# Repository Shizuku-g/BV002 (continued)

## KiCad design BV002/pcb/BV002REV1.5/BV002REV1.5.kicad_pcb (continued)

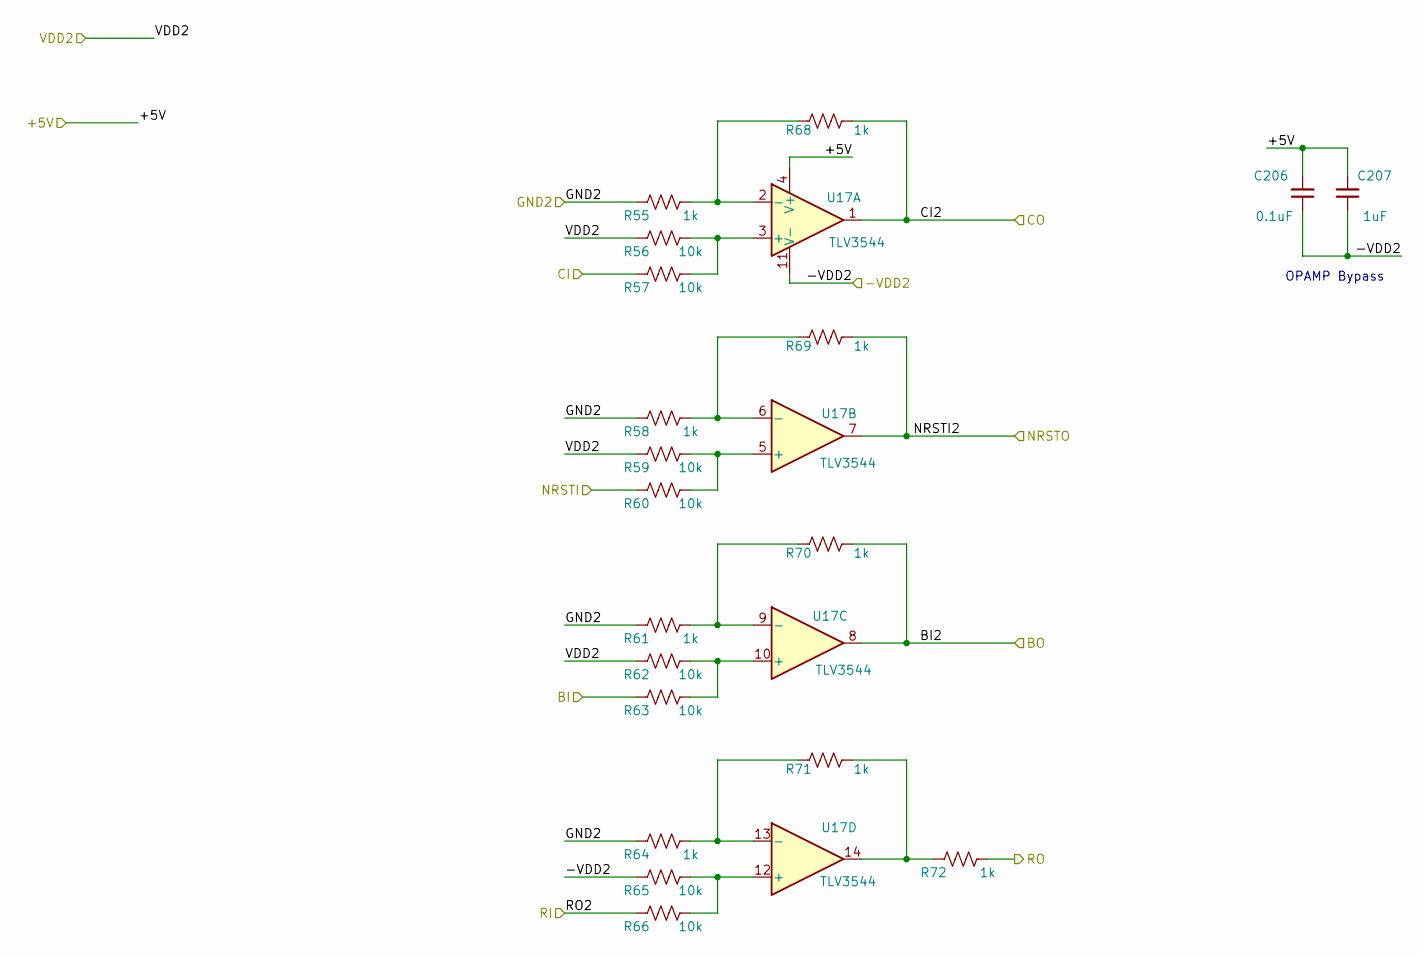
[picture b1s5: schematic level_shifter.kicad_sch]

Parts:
C206: 0.1uF; C_0402_1005Metric; PARTNO KGM05AR71C104KH
C207: 1uF; C_0402_1005Metric; PARTNO EMK105BJ105MV-F
R55, R58, R61, R64, R68, R69, R70, R71, R72: 1k; R_0402_1005Metric; PARTNO RC0402FR-071KL
R56, R57, R59, R60, R62, R63, R65, R66: 10k; R_0402_1005Metric; PARTNO RC0402JR-0710KL
U17: TLV3544; TSSOP-14_4.4x5mm_P0.65mm; PARTNO TLV3544IPWR

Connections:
+5V: C206.2, C207.2, U17.4 (V+); also elsewhere on the board
/BM1373/Level Shifter/BI: R63.1; also elsewhere on the board
/BM1373/Level Shifter/BI2: R70.1, U17.8; also elsewhere on the board
/BM1373/Level Shifter/CI: R57.1; also elsewhere on the board
/BM1373/Level Shifter/CI2: R68.1, U17.1; also elsewhere on the board
/BM1373/Level Shifter/NRSTI: R60.1; also elsewhere on the board
/BM1373/Level Shifter/NRSTI2: R69.1, U17.7; also elsewhere on the board
/BM1373/Level Shifter/RO: R72.1; also elsewhere on the board
/BM1373/Level Shifter/RO2: R66.1; also elsewhere on the board
unnamed: R71.1, R72.2, U17.14
unnamed: R56.1, R57.2, U17.3 (+)
unnamed: R55.1, R68.2, U17.2 (-)
unnamed: R59.2, R60.2, U17.5 (+)
unnamed: R58.1, R69.2, U17.6 (-)
unnamed: R62.2, R63.2, U17.10 (+)
unnamed: R61.1, R70.2, U17.9 (-)
unnamed: R65.2, R66.2, U17.12 (+)
unnamed: R64.1, R71.2, U17.13 (-)
VDD: R56.2, R59.1, R62.1; also elsewhere on the board
VDD1: R55.2, R58.2, R61.2, R64.2; also elsewhere on the board

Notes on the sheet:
OPAMP Bypass

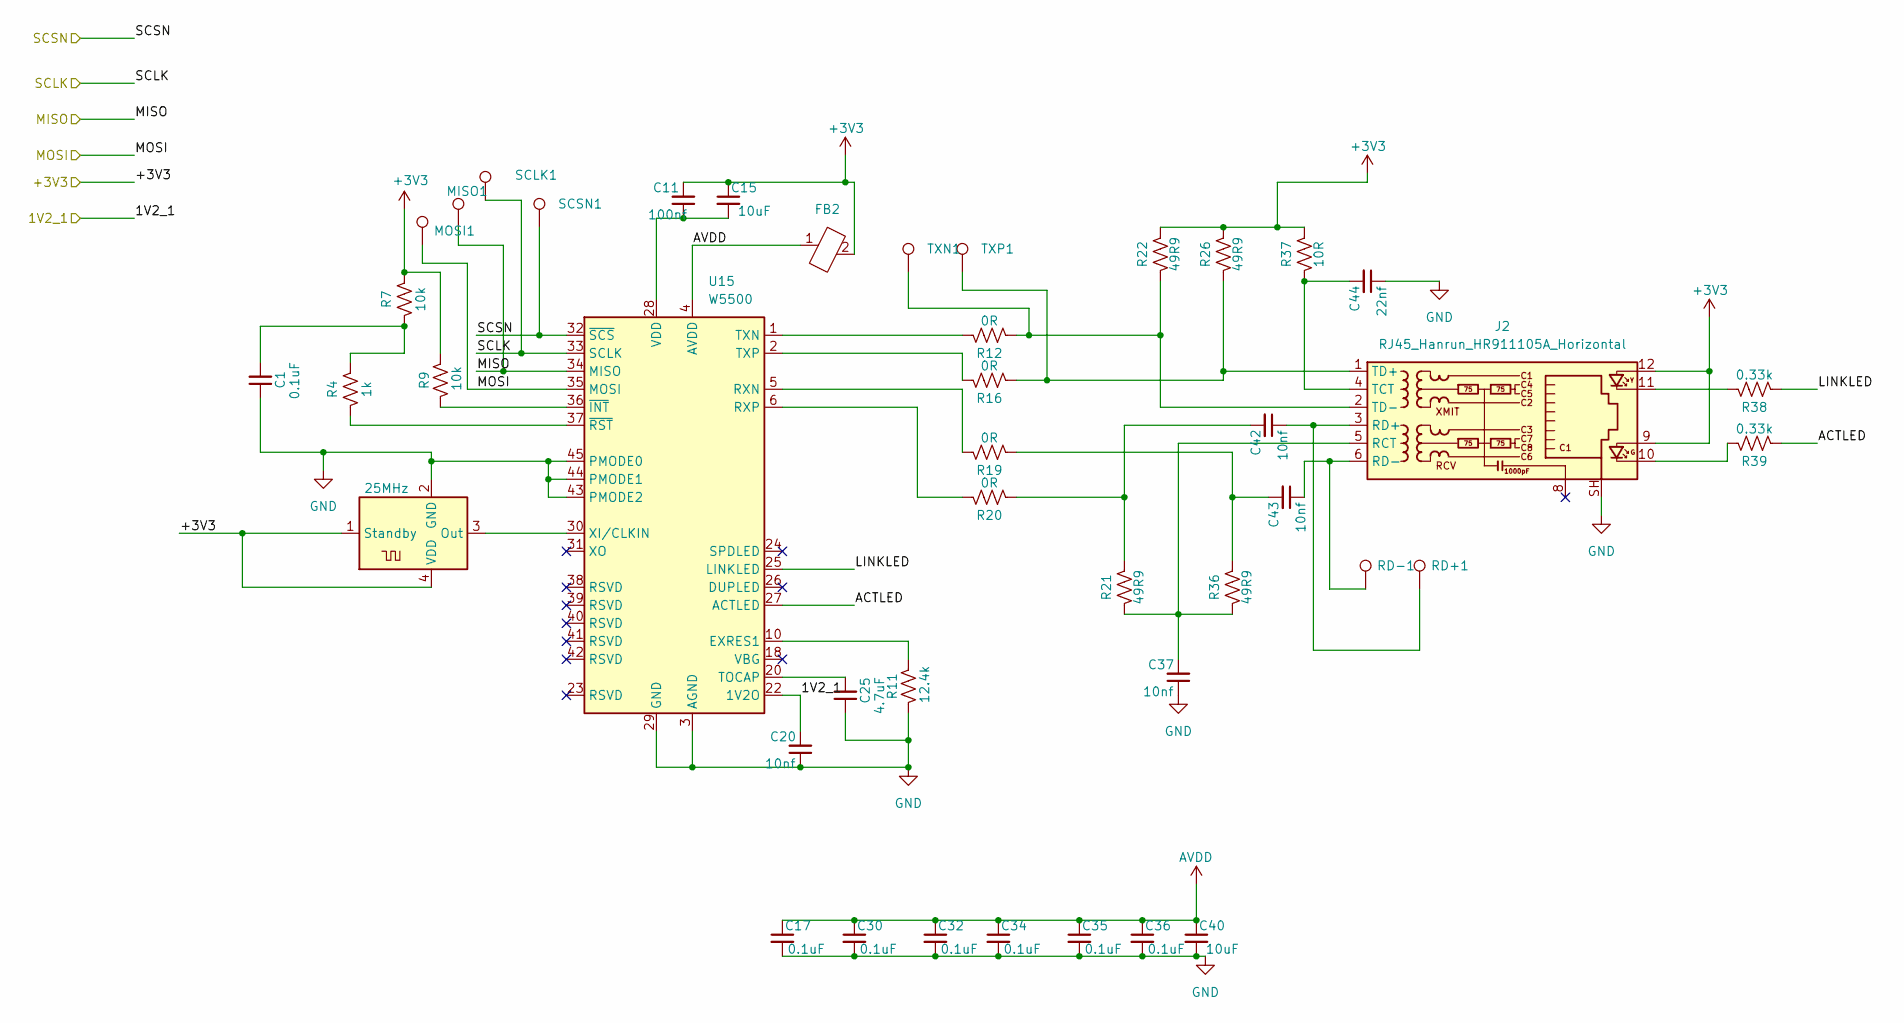
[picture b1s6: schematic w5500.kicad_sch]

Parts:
C1: 0.1uF; C_0402_1005Metric; PARTNO GRM155R61A475MEAAD
C11: 100nf; C_0402_1005Metric; PARTNO GRM188R61E106KA73D
C15, C40: 10uF; C_0603_1608Metric; PARTNO CL10A106MO8NQNC; LCSC C92487 Hot
C17, C30, C32, C34, C35, C36: 0.1uF; C_0603_1608Metric; PARTNO CL10A106MO8NQNC; LCSC C92487 Hot
C20, C37, C42, C43: 10nf; C_0402_1005Metric; PARTNO GRM188R61E106KA73D
C25: 4.7uF; C_0402_1005Metric; PARTNO GRM155R61A475MEAAD
C44: 22nf; C_0402_1005Metric; PARTNO GRM188R61E106KA73D
FB2: D_0201_0603Metric
J2: RJ45_Hanrun_HR911105A_Horizontal
MISO1: TestPoint_Pad_D1.5mm
MOSI1: TestPoint_Pad_D1.5mm
R4: 1k; R_0402_1005Metric; PARTNO RC0402FR-071KL; LCSC C106235
R7: 10k; R_0402_1005Metric; PARTNO RC0402FR-071KL; LCSC C106235
R9: 10k; R_0402_1005Metric; PARTNO RC0402FR-072KL; LCSC C60488
R11: 12.4k; R_0402_1005Metric; PARTNO RC0402FR-072KL; LCSC C60488
R12, R16, R19, R20: 0R; R_0402_1005Metric; PARTNO RC0402FR-071KL; LCSC C106235
R21, R22, R26, R36: 49R9; R_0402_1005Metric; PARTNO RC0402FR-071KL; LCSC C106235
R37: 10R; R_0402_1005Metric; PARTNO RC0402FR-071KL; LCSC C106235
R38, R39: 0.33k; R_0402_1005Metric; PARTNO RC0402FR-071KL; LCSC C106235
RD+1: TestPoint_Pad_D1.5mm
RD-1: TestPoint_Pad_D1.5mm
SCLK1: TestPoint_Pad_D1.5mm
SCSN1: TestPoint_Pad_D1.5mm
TXN1: TestPoint_Pad_D1.5mm
TXP1: TestPoint_Pad_D1.5mm
U2: 25MHz; Oscillator_SMD_EuroQuartz_XO32-4Pin_3.2x2.5mm; PARTNO SX3M25.000E20F30THN
U15: W5500; LQFP-48_7x7mm_P0.5mm

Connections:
1V2_1: C20.2, U15.22 (1V2O); also elsewhere on the board
/T-Display-S3/MISO: MISO1.1 (1_1), U15.34 (MISO); also elsewhere on the board
/T-Display-S3/MOSI: MOSI1.1 (1_1), U15.35 (MOSI); also elsewhere on the board
/T-Display-S3/SCLK: SCLK1.1 (1_1), U15.33 (SCLK); also elsewhere on the board
/T-Display-S3/SCSN: SCSN1.1 (1_1), U15.32 (~SCS); also elsewhere on the board
/T-Display-S3/W5500/ACTLED: R39.2, U15.27 (ACTLED)
/T-Display-S3/W5500/LINKLED: R38.2, U15.25 (LINKLED)
unnamed: C1.2, R4.1, R7.2
unnamed: C42.2, R20.2, R21.1
unnamed: C43.2, R19.2, R36.1
unnamed: J2.10, R39.1
unnamed: J2.11, R38.1
unnamed: C37.2, J2.5 (RCT), R21.2, R36.2
unnamed: C42.1, J2.3 (RD+), RD+1.1 (1_1)
unnamed: C43.1, J2.6 (RD-), RD-1.1 (1_1)
unnamed: C44.2, J2.4 (TCT), R37.2
unnamed: J2.1 (TD+), R16.2, R26.2, TXP1.1 (1_1)
unnamed: J2.2 (TD-), R12.2, R22.2, TXN1.1 (1_1)
unnamed: R11.2, U15.10 (EXRES1)
unnamed: R19.1, U15.5 (RXN)
unnamed: R20.1, U15.6 (RXP)
unnamed: C25.2, U15.20 (TOCAP)
unnamed: R12.1, U15.1 (TXN)
unnamed: R16.1, U15.2 (TXP)
unnamed: C11.1, C15.2, U15.28 (VDD)
unnamed: U2.3 (Out), U15.30 (XI/CLKIN)
unnamed: R9.1, U15.36 (~INT)
unnamed: R4.2, U15.37 (~RST)

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
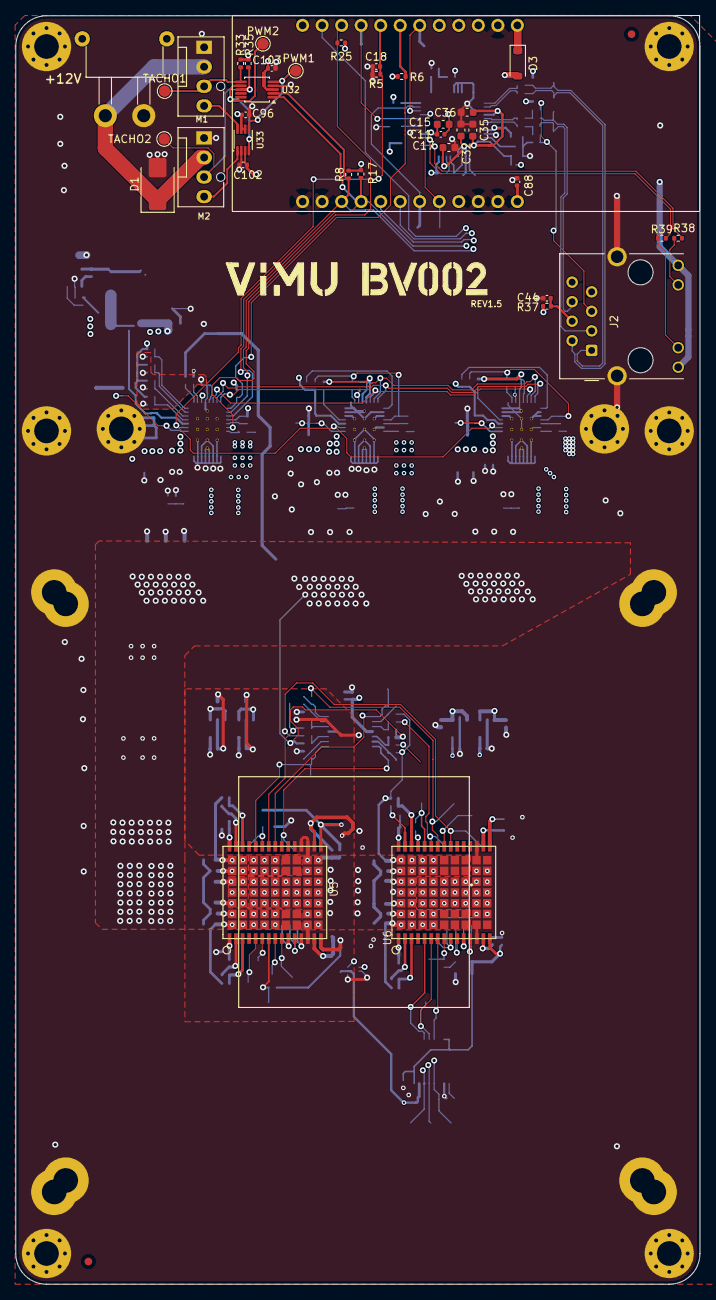
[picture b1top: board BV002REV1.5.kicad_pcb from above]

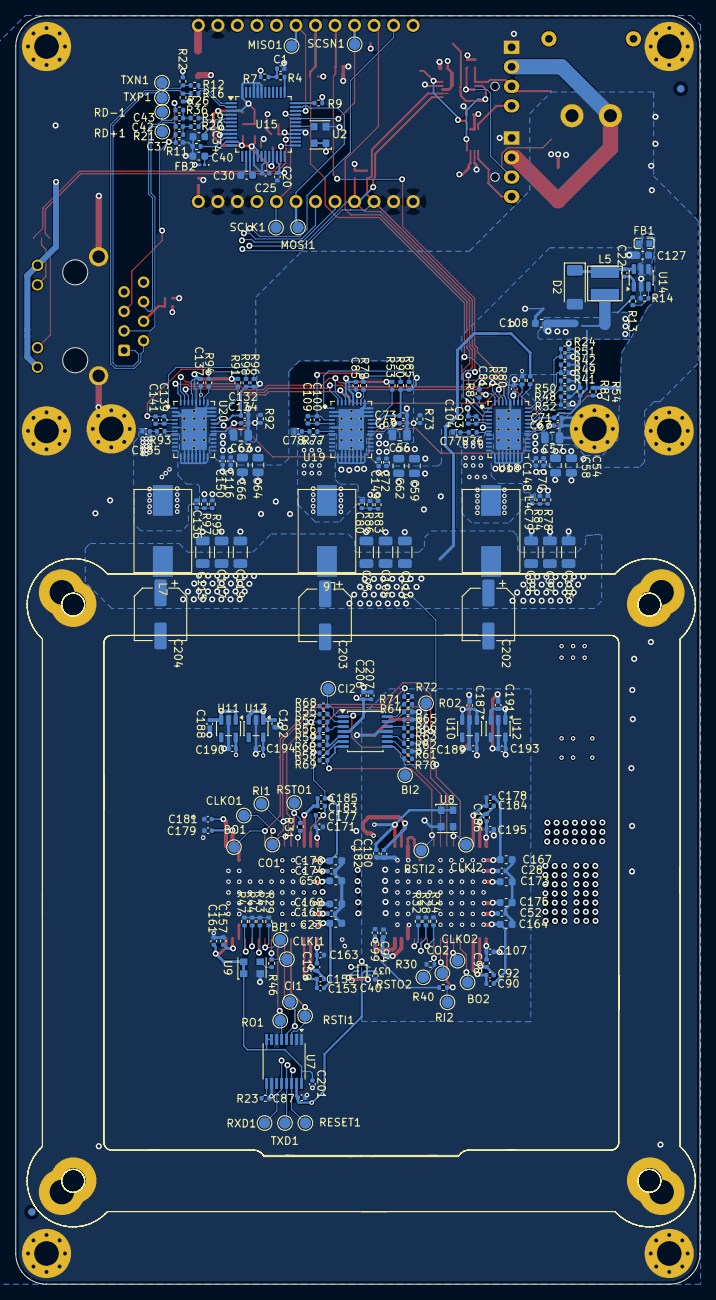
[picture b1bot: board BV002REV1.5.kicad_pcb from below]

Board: 4 copper layers, 89.0 x 165.0 mm, 289 parts (242 on the bottom side), 147 nets.

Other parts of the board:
C40#2: 10uF; C_0603_1608Metric
C201: 0.1uF; C_0402_1005Metric
C202, C203, C204: 270uF; CP_Elec_6.3x5.9
FID1, FID2, FID3, FID4: Fiducial_1mm_Mask2mm
H7, H8: MountingHole_Pad; MountingHole_3.2mm_M3_Pad_Via
R6: 10k; R_0402_1005Metric

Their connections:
1V2_1: C201.1; also elsewhere on the board
PGOOD: R6.1; also elsewhere on the board
VDD: C202.1, C203.1, C204.1; also elsewhere on the board

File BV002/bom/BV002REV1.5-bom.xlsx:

编号 | 位号 | 封装 | 数量 | 名称 | 供应商
1 | R46,R12,R16,R19,R20,R76,R77,R93 | R_0402_1005Metric 0R | 8
2 | R37,R54,R73,R78,R83,R84,R86,R92,R95,R97 | R_0402_1005Metric 10R | 10
3 | R21,R22,R26,R36,R80,R81 | R_0402_1005Metric 49R9 | 6
4 | R38,R39 | R_0402_1005Metric 0.33k | 2
5 | R4,R28,R32,R34,R43,R44,R47,R55,R58,R61,R64,R68,R69,R70,R71,R72 | R_0402_1005Metric 1k | 16
6 | R45 | R_0402_1005Metric 2k | 1
7 | R33,R35 | R_0402_1005Metric 2.7k | 2
8 | R51 | R_0402_1005Metric 4.64k | 1
9 | R8,R17,R25 | R_0402_1005Metric 4.7k | 3
10 | R87,R90,R98 | R_0402_1005Metric 5.11k | 3
11 | R52 | R_0402_1005Metric 6.81k | 1
12 | R5,R7,R9,R29,R30,R31,R40,R49,R53,R56,R57,R59,R60,R62,R63,R65,R66,R79,R82,R85,R9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 | R_0402_1005Metric 10k | 22
13 | R11 | R_0402_1005Metric 12.4k | 1
14 | R14 | R_0402_1005Metric 16.2k | 1
15 | R23 | R_0402_1005Metric 20k | 1
16 | R24,R91 | R_0402_1005Metric 21.5k | 2
17 | R48 | R_0402_1005Metric 31.6k | 1
18 | R42 | R_0402_1005Metric 15.4k | 1
19 | R13 | R_0402_1005Metric 84.5k | 1
20 | C50,C52,C81,C85,C137 | C_0402_1005Metric 33pF | 6
21 | C79,C80,C136 | C_0402_1005Metric 1000pF | 3
22 | C20,C22,C37,C42,C43 | C_0402_1005Metric 10nF | 5
23 | C44 | C_0402_1005Metric 22nF | 1
24 | C1,C11,C23,C28,C18,C77,C78,C86,C87,C88,C93,C96,C100,C102,C103,C135,C139,C148,C1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 | C_0402_1005Metric 100nF | 21
25 | C17,C30,C32,C34,C35,C36 | C_0603_1608Metric 100nF | 6
26 | C67,C69,C70,C72,C90,C92,C94,C98,C99,C107,C116,C132,C153,C155,C157,C159,C161,C16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 | C_0402_1005Metric 1uF | 39
27 | C104,C109,C141 | C_0402_1005Metric 2.2uF | 3
28 | C25,C71,C73,C134 | C_0402_1005Metric 4.7uF | 4
29 | C15,C40,C127,C164,C165,C167,C168,C173,C174,C175,C176 | C_0603_1005Metric 10uF | 11
30 | C54,C56,C57,C58,C59,C62,C63,C64,C66 | C_0805_2012Metric 10uf | 9
31 | C89,C95,C97,C105,C106,C114,C115,C117,C119 | C_1206_3216Metric 22uF | 9
32 | C121,C123,C138 | CAP, Aluminum Polymer, 560 uF, 0.003 ohm, SMD_7.3x1.9x4.3mm SMD | 3
33 | FB1 | BLM15AG121SN1D | 1
34 | FB2 | HH-1M1608-121JT | 1
35 | D1 | SMBJ18A | 1
36 | D2 | D_SOD-128,PMEG4030EP | 1
37 | D3 | D_SOD-123,1N5819 | 1
38 | L4,L6,L7 | SLC1175-30 0.68uH | 3
39 | L5 | L_Ferrocore_DLG-0703 4.7uH | 1
40 | U5,U6 | B1373CC | 2
41 | U14 | SOT-23-6,AP3211 | 1
42 | U18,U19,U20 | TPS546D24A | 3
43 | U32 | MSOP-10_3x3mm_P0.5mm,EMC2302-1 | 1
44 | U10, U11 | SOT-23-5,MCP1824T-1202E/OT | 2
45 | U12, U13 | SOT-23-5,MCP1824T-0802E | 2
46 | U30 | T-Display-S3 | 1
47 | U17 | TLV3544 | 1
48 | U37 | TMP1075 | 1
49 | U33 | TXU0102-DCU | 1
50 | U15 | W5500 | 1
51 | J1 | XT30 | 1
52 | J2 | RJ45_Hanrun_HR911105A_Horizontal | 1
53 | J5,J6 | Conn_01x12-Socket | 2
54 | J7,J8 | Conn_01x12-Header | 2
55 | M1,M2 | Fan_4pin | 2

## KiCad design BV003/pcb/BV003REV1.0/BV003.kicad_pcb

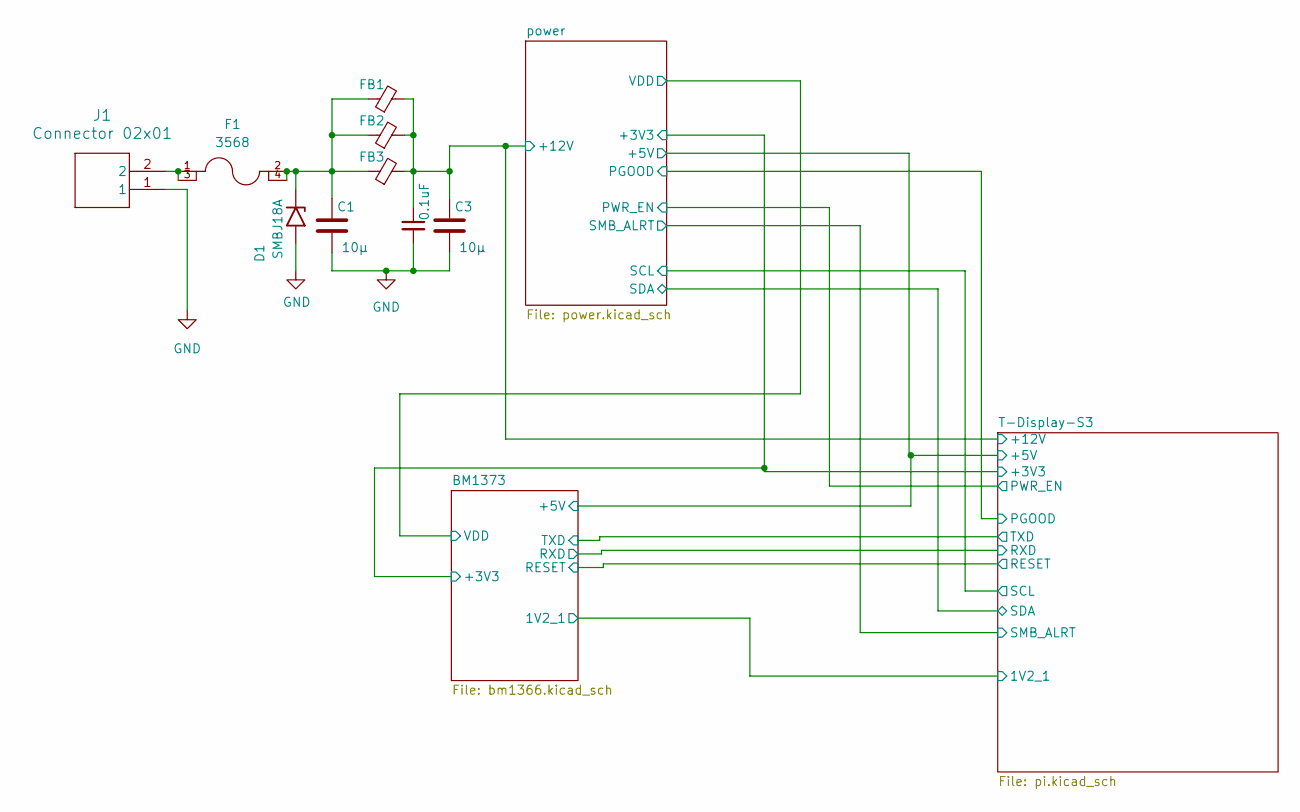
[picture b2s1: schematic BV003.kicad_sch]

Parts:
C1, C3: 10µ; C_1210_3225Metric_Pad1.33x2.70mm_HandSolder; LCSC C89632
C2: 0.1uF; C_0603_1608Metric; PARTNO CL10A106MO8NQNC; LCSC C92487
D1: SMBJ18A; D_SMB; LCSC C113985
F1: 3568; Fuseholder Blade_3568; LCSC C5249699
FB1, FB2, FB3: BLE32SN120SN1L; R_1210_3225Metric_Pad1.30x2.65mm_HandSolder; LCSC C5597997
J1: Connector 02x01; AMASS_XT60PW-M_1x02_P7.20mm_Horizontal; LCSC C98732

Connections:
GND: C1.2, C2.2, C3.2, D1.2 (A2), J1.1; also elsewhere on the board

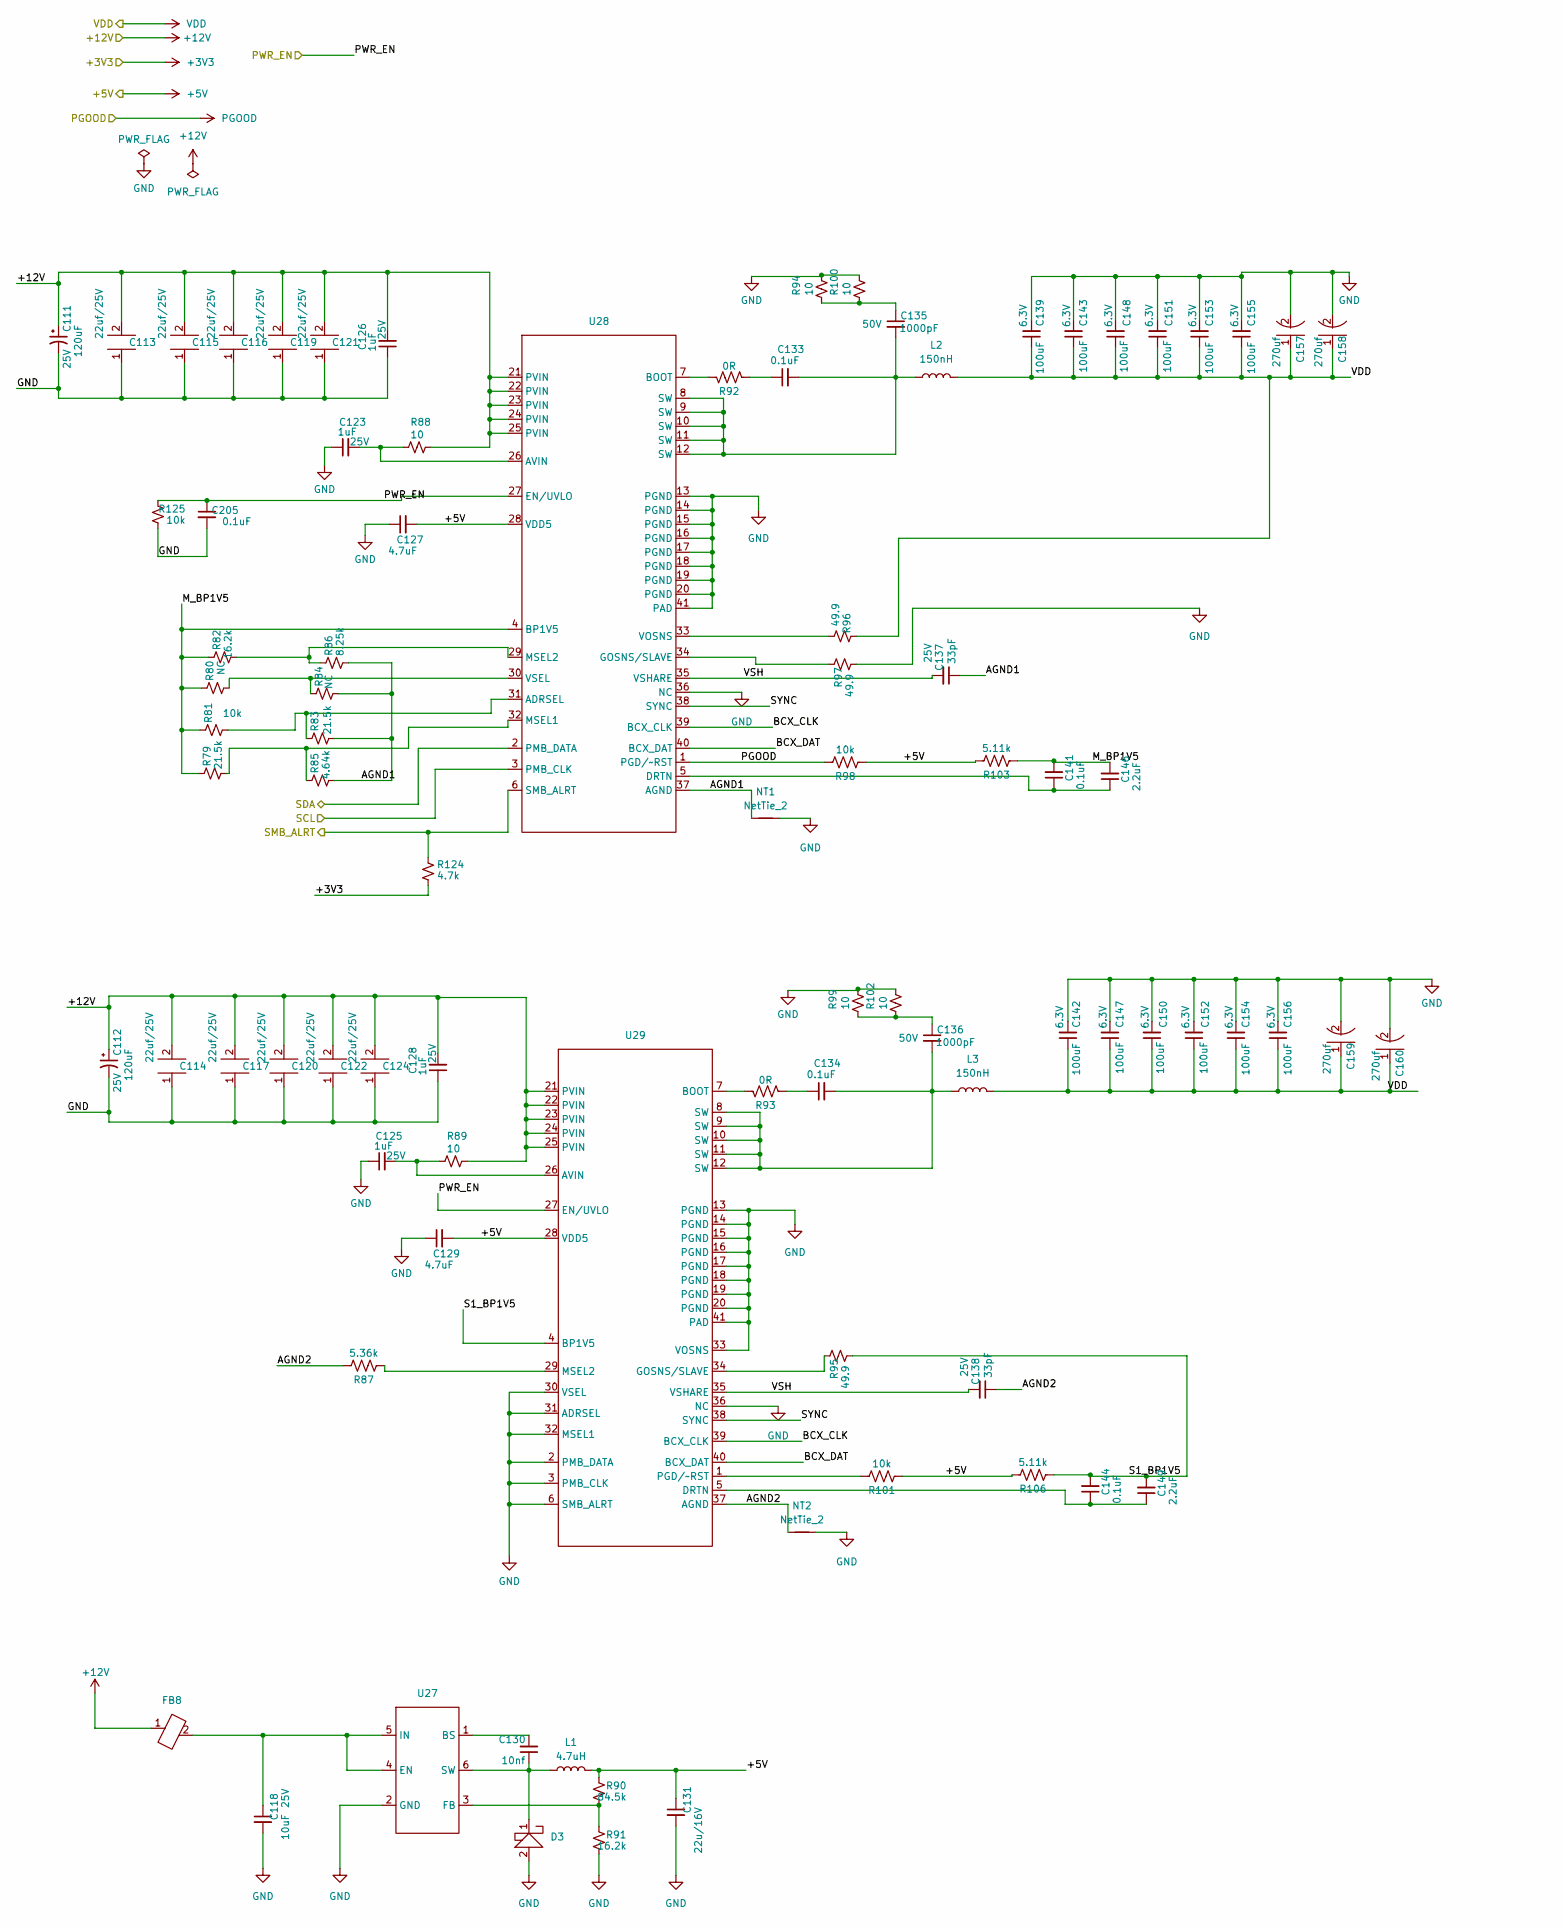
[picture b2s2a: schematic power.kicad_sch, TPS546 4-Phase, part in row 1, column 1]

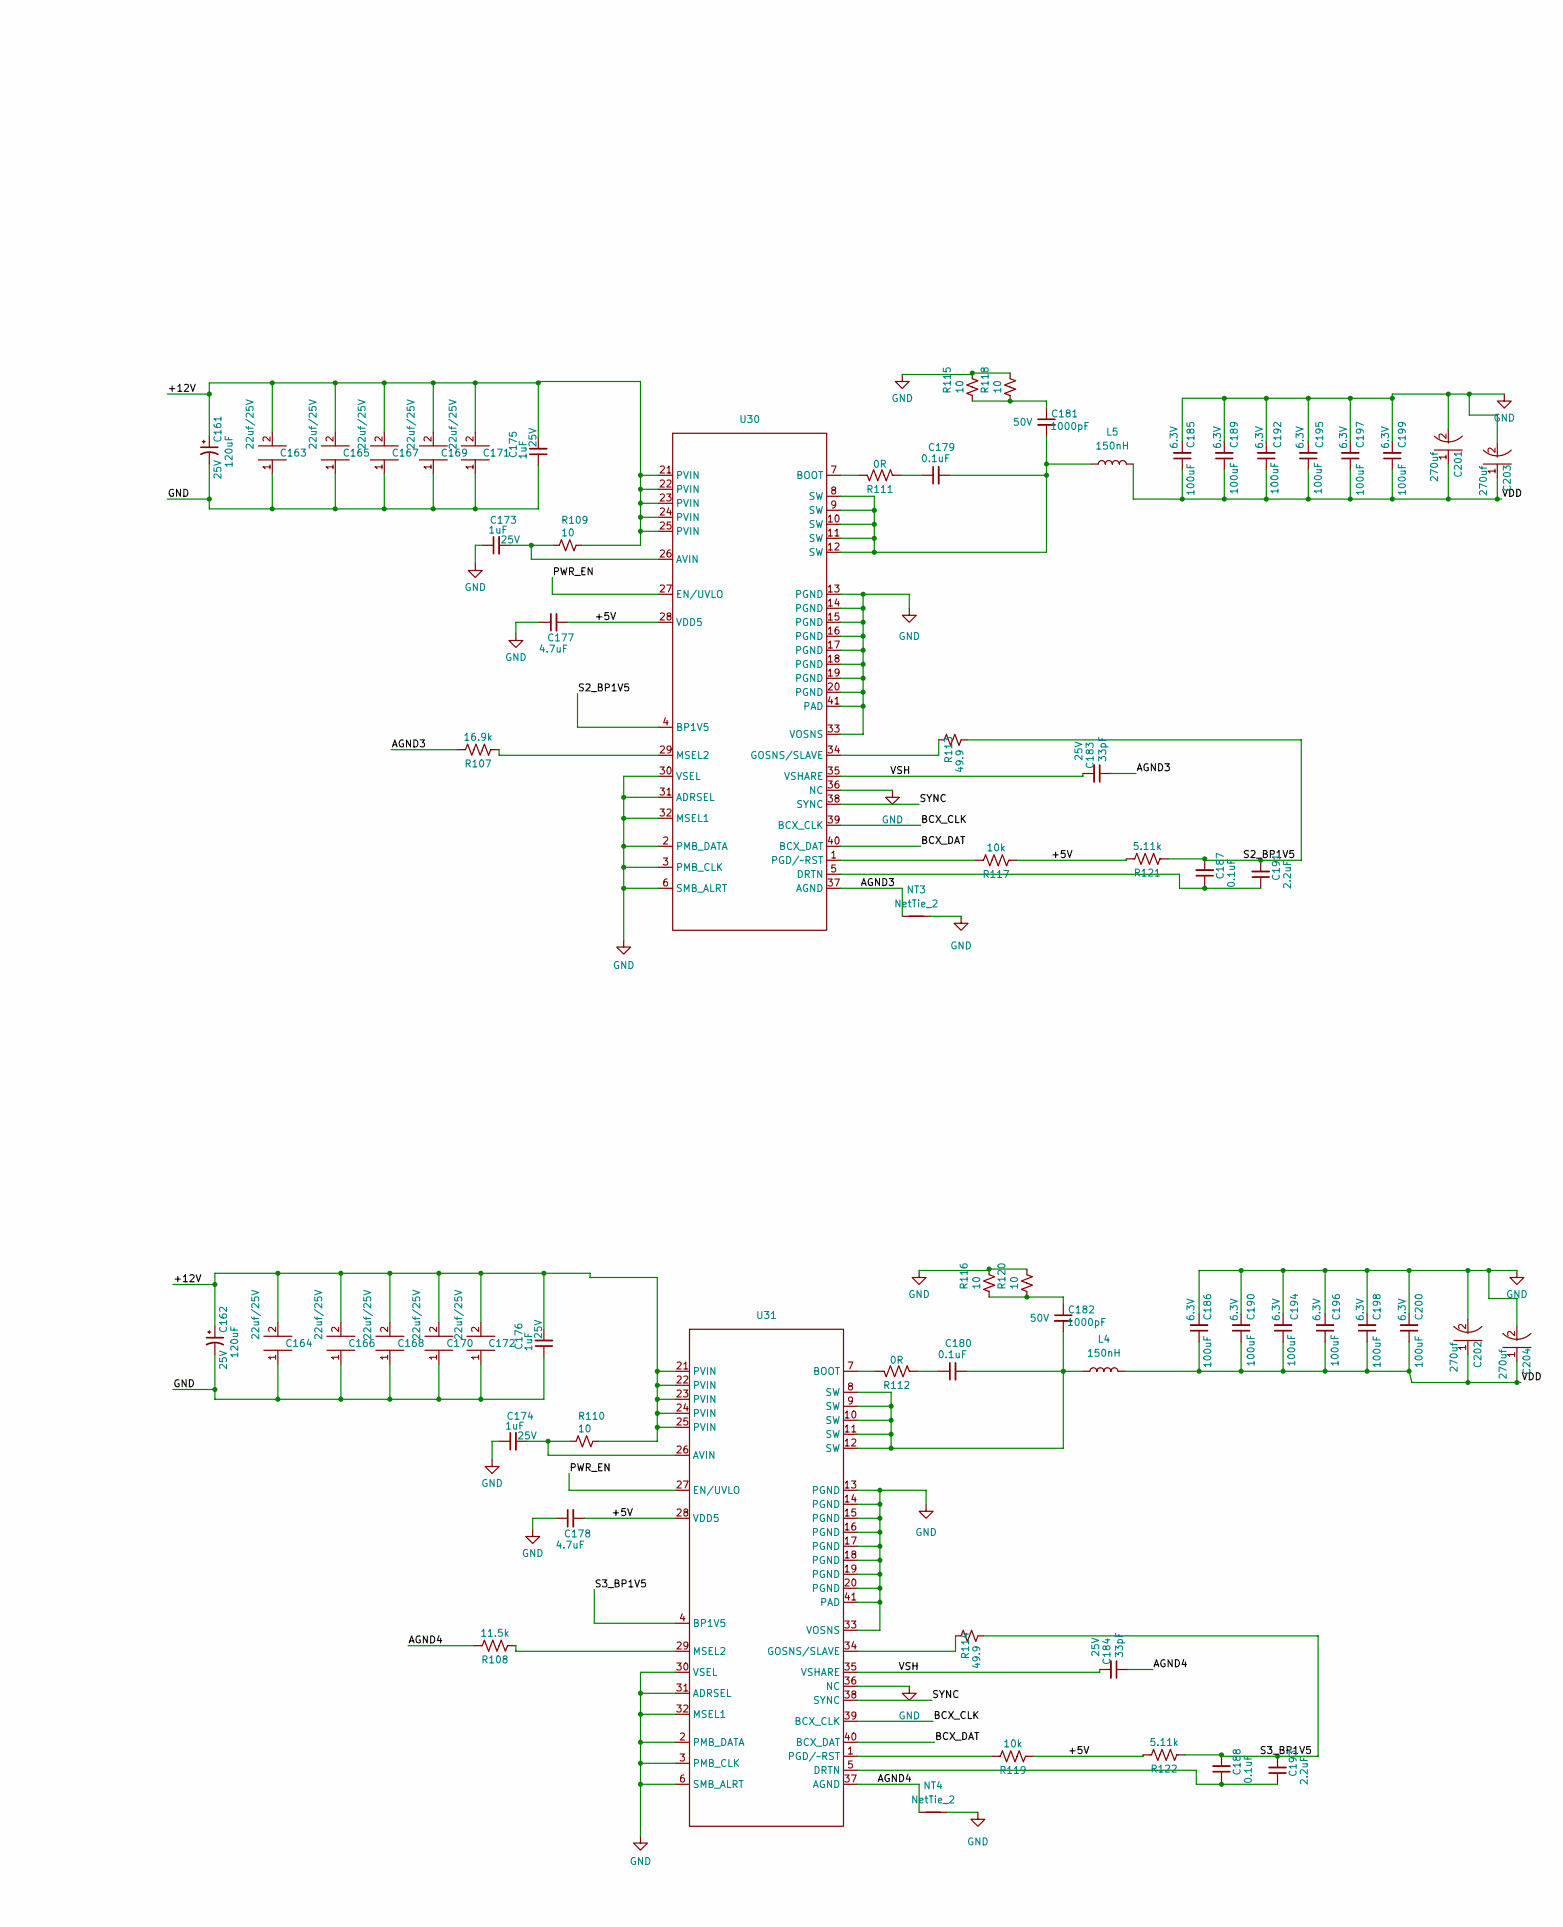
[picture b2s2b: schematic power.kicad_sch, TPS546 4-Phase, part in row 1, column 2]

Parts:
C111, C112, C161, C162: 120uF; CP_Elec_6.3x5.9; Voltage 25V
C113, C114, C115, C116, C117, C119, C120, C121, C122, C124, C163, C164, C165, C166, C167, C168, C169, C170, C171, C172: 22uf/25V; C_0805_2012Metric
C118: 10uF; C_0603_1608Metric; Voltage 25V; PARTNO GRM188R61E106KA73D
C123, C125, C126, C128, C173, C174, C175, C176: 1uF; C_0402_1005Metric; Voltage 25V; PARTNO TMK107B7105KA-T
C127, C129, C177, C178: 4.7uF; C_0402_1005Metric; PARTNO GRM155R61A475MEAAD
C130: 10nf; C_0402_1005Metric; PARTNO GRM188R61E106KA73D
C131: 22u/16V; C_0603_1608Metric; PARTNO GRM188R61E106KA73D
C133, C134, C179, C180, C205: 0.1uF; C_0402_1005Metric; PARTNO KGM05AR71C104KH
C135, C136, C181, C182: 1000pF; C_0402_1005Metric; Voltage 50V; PARTNO CC0402JRNPO9BN101
C137, C138, C183, C184: 33pF; C_0402_1005Metric; Voltage 25V; PARTNO KGM05ACG1E330JH
C139, C142, C143, C147, C148, C150, C151, C152, C153, C154, C155, C156, C185, C186, C189, C190, C192, C194, C195, C196, C197, C198, C199, C200: 100uF; C_1206_3216Metric; Voltage 6.3V; PARTNO CL31A107MQHNNNE
C141, C144, C187, C188: 0.1uF; C_0402_1005Metric; PARTNO GRM155R61A475MEAAD
C146, C149, C191, C193: 2.2uF; C_0402_1005Metric; PARTNO GRM155R61A475MEAAD
C157, C158, C159, C160, C201, C202, C203, C204: 270uf; CP_Elec_6.3x5.9
D3: D_SOD-128
FB8: D_0201_0603Metric
L1: 4.7uH; L_Ferrocore_DLG-0703; PARTNO FTC201612S1R5MBCA
L2, L3, L4, L5: 150nH; SLC1175-271MEC_COC; PARTNO SLC1175-301
NT1, NT2, NT3, NT4: NetTie_2; NetTie-2_SMD_Pad0.2mmx1mm
R79, R83: 21.5k; R_0402_1005Metric; PARTNO RC0402JR-0710KL
R80, R84: NC; R_0402_1005Metric; PARTNO RC0402JR-0710KL
R81, R125: 10k; R_0402_1005Metric; PARTNO RC0402JR-0710KL
R82: 16.2k; R_0402_1005Metric; PARTNO RC0402JR-0710KL
R85: 4.64k; R_0402_1005Metric; PARTNO RC0402JR-0710KL
R86: 8.25k; R_0402_1005Metric; PARTNO RC0402JR-0710KL
R87: 5.36k; R_0402_1005Metric; PARTNO RC0402DR-0710KL; LCSC C471764
R88, R89, R94, R99, R100, R102, R109, R110, R115, R116, R118, R120: 10; R_0402_1005Metric; PARTNO RC0402FR-0710RL
R90: 84.5k; R_0402_1005Metric; PARTNO RC0402FR-0752K3L
R91: 16.2k; R_0402_1005Metric; PARTNO RC0402FR-0752K3L
R92, R93, R111, R112: 0R; R_0402_1005Metric; PARTNO RC0402FR-071KL; LCSC C106235
R95, R96, R97, R113, R114: 49.9; R_0402_1005Metric; PARTNO RC0402FR-0749R9L
R98, R101, R117, R119: 10k; R_0402_1005Metric; PARTNO RC0402DR-0710KL; LCSC C471764
R103, R106, R121, R122: 5.11k; R_0402_1005Metric; PARTNO RC0402DR-0710KL; LCSC C471764
R107: 16.9k; R_0402_1005Metric; PARTNO RC0402DR-0710KL; LCSC C471764
R108: 11.5k; R_0402_1005Metric; PARTNO RC0402DR-0710KL; LCSC C471764
R124: 4.7k; R_0402_1005Metric; PARTNO RC0402JR-074K7L
U27: SOT-23-6
U28, U29, U30, U31: LQFN40-CLIP

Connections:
+3V3: R124.2, U28.2 (PMB_DATA); also elsewhere on the board
+5V: C127.2, C129.2, C131.1, C177.2, C178.2, L1.2, R90.2, R98.1, R101.1, R103.2, R106.2, R117.1, R119.1, R121.2, R122.2, U28.28 (VDD5), U29.28 (VDD5), U30.28 (VDD5), U31.28 (VDD5); also elsewhere on the board
/T-Display-S3/SCL: U28.3 (PMB_CLK); also elsewhere on the board
/T-Display-S3/SMB_ALRT: R124.1, U28.6 (SMB_ALRT); also elsewhere on the board
/power1/AGND1: C137.1, NT1.2, R83.1, R84.1, R85.1, R86.1, U28.37 (AGND)
/power1/AGND2: C138.1, NT2.2, R87.2, U29.37 (AGND)
/power1/AGND3: C183.1, NT3.2, R107.2, U30.37 (AGND)
/power1/AGND4: C184.1, NT4.2, R108.2, U31.37 (AGND)
/power1/BCX_CLK: U28.39 (BCX_CLK), U29.39 (BCX_CLK), U30.39 (BCX_CLK), U31.39 (BCX_CLK)
/power1/BCX_DAT: U28.40 (BCX_DAT), U29.40 (BCX_DAT), U30.40 (BCX_DAT), U31.40 (BCX_DAT)
/power1/M_BP1V5: C141.2, C146.2, R79.2, R80.2, R81.2, R82.2, R103.1, U28.4 (BP1V5)
/power1/PWR_EN: C205.1, R125.2, U28.27 (EN/UVLO), U29.27 (EN/UVLO), U30.27 (EN/UVLO), U31.27 (EN/UVLO); also elsewhere on the board
/power1/S1_BP1V5: C144.2, C149.2, R95.2, R106.1, U29.4 (BP1V5)
/power1/S2_BP1V5: C187.2, C191.2, R113.2, R121.1, U30.4 (BP1V5)
/power1/S3_BP1V5: C188.2, C193.2, R114.2, R122.1, U31.4 (BP1V5)
/power1/SYNC: U28.38 (SYNC), U29.38 (SYNC), U30.38 (SYNC), U31.38 (SYNC)
/power1/VSH: C137.2, C138.2, C183.2, C184.2, U28.35 (VSHARE), U29.35 (VSHARE), U30.35 (VSHARE), U31.35 (VSHARE)
GND: C111.2, C112.2, C113.1, C114.1, C115.1, C116.1, C117.1, C118.2, C119.1, C120.1, C121.1, C122.1, C123.1, C124.1, C125.1, C126.1, C127.1, C128.1, C129.1, C131.2, C139.2, C142.2, C143.2, C147.2, C148.2, C150.2, C151.2, C152.2, C153.2, C154.2, C155.2, C156.2, C157.2, C158.2, C159.2, C160.2, C161.2, C162.2, C163.1, C164.1, C165.1, C166.1, C167.1, C168.1, C169.1, C170.1, C171.1, C172.1, C173.1, C174.1, C175.1, C176.1, C177.1, C178.1, C185.2, C186.2, C189.2, C190.2, C192.2, C194.2, C195.2, C196.2, C197.2, C198.2, C199.2, C200.2, C201.2, C202.2, C203.2, C204.2, C205.2, D3.2, NT1.1, NT2.1, NT3.1, NT4.1, R91.1, R94.1, R97.2, R99.1, R100.1, R102.1, R115.1, R116.1, R118.1, R120.1, R125.1, U27.2 (GND), U28.13 (PGND), U28.14 (PGND), U28.15 (PGND), U28.16 (PGND), U28.17 (PGND), U28.18 (PGND), U28.19 (PGND), U28.20 (PGND), U28.36 (NC), U28.41 (PAD), U29.2 (PMB_DATA), U29.3 (PMB_CLK), U29.6 (SMB_ALRT), U29.13 (PGND), U29.14 (PGND), U29.15 (PGND), U29.16 (PGND), U29.17 (PGND), U29.18 (PGND), U29.19 (PGND), U29.20 (PGND), U29.30 (VSEL), U29.31 (ADRSEL), U29.32 (MSEL1), U29.33 (VOSNS), U29.36 (NC), U29.41 (PAD), U30.2 (PMB_DATA), U30.3 (PMB_CLK), U30.6 (SMB_ALRT), U30.13 (PGND), U30.14 (PGND), U30.15 (PGND), U30.16 (PGND), U30.17 (PGND), U30.18 (PGND), U30.19 (PGND), U30.20 (PGND), U30.30 (VSEL), U30.31 (ADRSEL), U30.32 (MSEL1), U30.33 (VOSNS), U30.36 (NC), U30.41 (PAD), U31.2 (PMB_DATA), U31.3 (PMB_CLK), U31.6 (SMB_ALRT), U31.13 (PGND), U31.14 (PGND), U31.15 (PGND), U31.16 (PGND), U31.17 (PGND), U31.18 (PGND), U31.19 (PGND), U31.20 (PGND), U31.30 (VSEL), U31.31 (ADRSEL), U31.32 (MSEL1), U31.33 (VOSNS), U31.36 (NC), U31.41 (PAD); also elsewhere on the board
unnamed: C133.1, R92.2
unnamed: C133.2, C135.2, L2.1, U28.8 (SW), U28.9 (SW), U28.10 (SW), U28.11 (SW), U28.12 (SW)
unnamed: C134.1, R93.2
unnamed: C134.2, C136.2, L3.1, U29.8 (SW), U29.9 (SW), U29.10 (SW), U29.11 (SW), U29.12 (SW)
unnamed: C135.1, R94.2, R100.2
unnamed: C136.1, R99.2, R102.2
unnamed: C179.1, R111.2
unnamed: C179.2, C181.2, L5.1, U30.8 (SW), U30.9 (SW), U30.10 (SW), U30.11 (SW), U30.12 (SW)
unnamed: C180.1, R112.2
unnamed: C180.2, C182.2, L4.1, U31.8 (SW), U31.9 (SW), U31.10 (SW), U31.11 (SW), U31.12 (SW)
unnamed: C181.1, R115.2, R118.2
unnamed: C182.1, R116.2, R120.2
unnamed: C130.2, U27.1 (BS)
unnamed: C118.1, FB8.2, U27.4 (EN), U27.5 (IN)
unnamed: R90.1, R91.2, U27.3 (FB)
unnamed: C130.1, D3.1, L1.1, U27.6 (SW)
unnamed: R81.1, R83.2, U28.31 (ADRSEL)
unnamed: C123.2, R88.2, U28.26 (AVIN)
unnamed: R92.1, U28.7 (BOOT)
unnamed: C141.1, C146.1, U28.5 (DRTN)
unnamed: R97.1, U28.34 (GOSNS/SLAVE)
unnamed: R79.1, R85.2, U28.32 (MSEL1)
unnamed: R82.1, R86.2, U28.29 (MSEL2)
unnamed: R96.2, U28.33 (VOSNS)
unnamed: R80.1, R84.2, U28.30 (VSEL)
unnamed: C125.2, R89.2, U29.26 (AVIN)
unnamed: R93.1, U29.7 (BOOT)
unnamed: C144.1, C149.1, U29.5 (DRTN)
unnamed: R95.1, U29.34 (GOSNS/SLAVE)
unnamed: R87.1, U29.29 (MSEL2)
unnamed: R101.2, U29.1 (PGD/~RST)
unnamed: C173.2, R109.2, U30.26 (AVIN)
unnamed: R111.1, U30.7 (BOOT)
unnamed: C187.1, C191.1, U30.5 (DRTN)
unnamed: R113.1, U30.34 (GOSNS/SLAVE)
unnamed: R107.1, U30.29 (MSEL2)
unnamed: R117.2, U30.1 (PGD/~RST)
unnamed: C174.2, R110.2, U31.26 (AVIN)
unnamed: R112.1, U31.7 (BOOT)
unnamed: C188.1, C193.1, U31.5 (DRTN)
unnamed: R114.1, U31.34 (GOSNS/SLAVE)
unnamed: R108.1, U31.29 (MSEL2)
unnamed: R119.2, U31.1 (PGD/~RST)
PGOOD: R98.2, U28.1 (PGD/~RST); also elsewhere on the board
VDD: C139.1, C142.1, C143.1, C147.1, C148.1, C150.1, C151.1, C152.1, C153.1, C154.1, C155.1, C156.1, C157.1, C158.1, C159.1, C160.1, C185.1, C186.1, C189.1, C190.1, C192.1, C194.1, C195.1, C196.1, C197.1, C198.1, C199.1, C200.1, C201.1, C202.1, C203.1, C204.1, L2.2, L3.2, L4.2, L5.2, R96.1; also elsewhere on the board
